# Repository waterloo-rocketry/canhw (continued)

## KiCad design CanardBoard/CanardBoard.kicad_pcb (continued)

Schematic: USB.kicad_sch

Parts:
C47: 22uF; C_0805_2012Metric
C48: 0.1uF; C_0402_1005Metric
F7: 1.5A; Fuse_0805_2012Metric
J9: USB_C_Receptacle_USB2.0_16P; USB_C_Receptacle_GCT_USB4105-xx-A_16P_TopMnt_Horizontal
R45, R46: 5.1k; R_0402_1005Metric; LCSC Part # C17630
U7: USBLC6-2SC6; SOT-23-6

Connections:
+5V_USB: C47.1, C48.1, F7.1, U7.5 (VBUS); also elsewhere on the board
/Processor/USB_D+: U7.4 (I/O2); also elsewhere on the board
/Processor/USB_D-: U7.6 (I/O1); also elsewhere on the board
GND: C47.2, C48.2, J9.A1 (GND), J9.A12 (GND), J9.B1 (GND), J9.B12 (GND), J9.S1 (SHIELD), R45.2, R46.2, U7.2 (GND); also elsewhere on the board
unnamed: F7.2, J9.A4 (VBUS), J9.A9 (VBUS), J9.B4 (VBUS), J9.B9 (VBUS)
unnamed: J9.A5 (CC1), R46.1
unnamed: J9.B5 (CC2), R45.1
unnamed: J9.A6 (D+), J9.B6 (D+), U7.3 (I/O2)
unnamed: J9.A7 (D-), J9.B7 (D-), U7.1 (I/O1)

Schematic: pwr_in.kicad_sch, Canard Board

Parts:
C19, C20, C25, C26: 0.1uF; C_0603_1608Metric; LCSC Part # C49678
C21, C22, C23, C24, C33, C34: 0.1uF; C_0402_1005Metric; LCSC Part # C49678
C27, C28, C29, C30: 10nF; C_0402_1005Metric; LCSC Part # C49678
C31, C32: 0.1uF; C_0805_2012Metric; LCSC Part # C49678
C35, C36: 10uF; C_1210_3225Metric; LCSC Part # C49678
D2, D3: SMAJ28CA; D_SMA
D4, D5, D6, D7: RB520S30T1G; D_SOD-523
F1, F2: 20A; Fuse_1206_3216Metric
J3, J4: XT30PW-M; AMASS_XT30PW-M
Q1, Q2, Q3, Q4: SIR626DP-T1-RE3; PowerPAK_SO-8_Single
Q5, Q6: 2N7002W; Manufacturer_Part_Number 2N7002W
R13, R15, R17, R19, R21, R23, R35, R36, R39, R40: 100k; R_0402_1005Metric; LCSC Part # C17630
R14, R16, R33, R34, R41, R42: 10k; R_0402_1005Metric; LCSC Part # C17630
R18, R20: 3.16k; R_0402_1005Metric; LCSC Part # C17630
R22, R24: 2.2k; R_0402_1005Metric; LCSC Part # C17630
R25, R26: 0R; R_0402_1005Metric; LCSC Part # C17630
R27, R28: 100R; R_0402_1005Metric; LCSC Part # C17630
R29, R30: 1mR; R_Shunt_Vishay_WSKW0612; MPN WSKW06121L000FEA
R31, R32: 10R; R_0402_1005Metric; LCSC Part # C17630
R37, R38: 33k; R_0402_1005Metric; LCSC Part # C17630
TP11: VBAT; TestPoint_Pad_D1.0mm
U4, U5: LM749x0; Manufacturer_Part_Number LM74910QRGERQ1

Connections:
+3V3: D4.1 (K), D6.1 (K), R33.2, R34.2; also elsewhere on the board
+VBAT: C35.1, C36.1, Q3.S, Q4.S, TP11.1, U4.15 (OUT), U5.15 (OUT); also elsewhere on the board
/Power Input/BAT1_IN: C19.1, D2.2 (A2), F1.1, Q1.S, R13.1, R39.1, U4.2 (A)
/Power Input/BAT2_IN: C20.1, D3.2 (A2), F2.1, Q2.S, R15.1, R40.1, U5.2 (A)
/Power Input/BAT_FLT1: R33.1, U4.12 (~FLT); also elsewhere on the board
/Power Input/BAT_FLT2: R34.1, U5.12 (~FLT); also elsewhere on the board
/Power Input/ISENS_BAT1: R37.1, U4.10 (IMON); also elsewhere on the board
/Power Input/ISENS_BAT2: R38.1, U5.10 (IMON); also elsewhere on the board
/Power Input/PWR_EN: Q5.1 (G), Q6.1 (G), R41.2, R42.2; also elsewhere on the board
/Power Input/VSENS_BAT1: D4.2 (A), D5.1 (K), R13.2, R14.1; also elsewhere on the board
/Power Input/VSENS_BAT2: D6.2 (A), D7.1 (K), R15.2, R16.1; also elsewhere on the board
GND: C19.2, C20.2, C21.2, C22.2, C25.2, C26.2, C31.2, C32.2, C33.2, C34.2, C35.2, C36.2, D2.1 (A1), D3.1 (A1), D5.2 (A), D7.2 (A), J3.N, J4.N, Q5.2 (S), Q6.2 (S), R14.2, R16.2, R18.2, R20.2, R22.2, R24.2, R35.2, R36.2, R37.2, R38.2, R41.1, R42.1, U4.13 (GND), U5.13 (GND); also elsewhere on the board
unnamed: C31.1, R31.2
unnamed: C32.1, R32.2
unnamed: F1.2, J3.P
unnamed: F2.2, J4.P
unnamed: Q3.D, R29.1
unnamed: Q4.D, R30.1
unnamed: Q5.3 (D), R39.2, U4.6 (EN), U4.7 (~SLEEP)
unnamed: Q6.3 (D), R40.2, U5.6 (EN), U5.7 (~SLEEP)
unnamed: R27.1, R29.3
unnamed: R28.1, R30.3
unnamed: C23.1, C25.1, Q1.D, R25.1, R29.4, U4.16 (SLEEP_OV), U4.22 (VS), U4.24 (C)
unnamed: C23.2, U4.23 (CAP)
unnamed: C27.1, R27.2, U4.20 (CS+)
unnamed: C27.2, C28.2, R29.2, U4.19 (CS-)
unnamed: Q1.G, U4.1 (DGATE)
unnamed: Q3.G, R31.1, U4.14 (HGATE)
unnamed: R35.1, U4.11 (ILIM)
unnamed: C28.1, R25.2, U4.18 (ISCP)
unnamed: R21.2, R22.1, U4.5 (OV)
unnamed: R17.1, R21.1, U4.3 (SW)
unnamed: C33.1, U4.9 (TMR)
unnamed: C21.1, R17.2, R18.1, U4.4 (UVLO)
unnamed: C24.1, C26.1, Q2.D, R26.1, R30.4, U5.16 (SLEEP_OV), U5.22 (VS), U5.24 (C)
unnamed: C24.2, U5.23 (CAP)
unnamed: C29.1, R28.2, U5.20 (CS+)
unnamed: C29.2, C30.2, R30.2, U5.19 (CS-)
unnamed: Q2.G, U5.1 (DGATE)
unnamed: Q4.G, R32.1, U5.14 (HGATE)
unnamed: R36.1, U5.11 (ILIM)
unnamed: C30.1, R26.2, U5.18 (ISCP)
unnamed: R23.2, R24.1, U5.5 (OV)
unnamed: R19.1, R23.1, U5.3 (SW)
unnamed: C34.1, U5.9 (TMR)
unnamed: C22.1, R19.2, R20.1, U5.4 (UVLO)

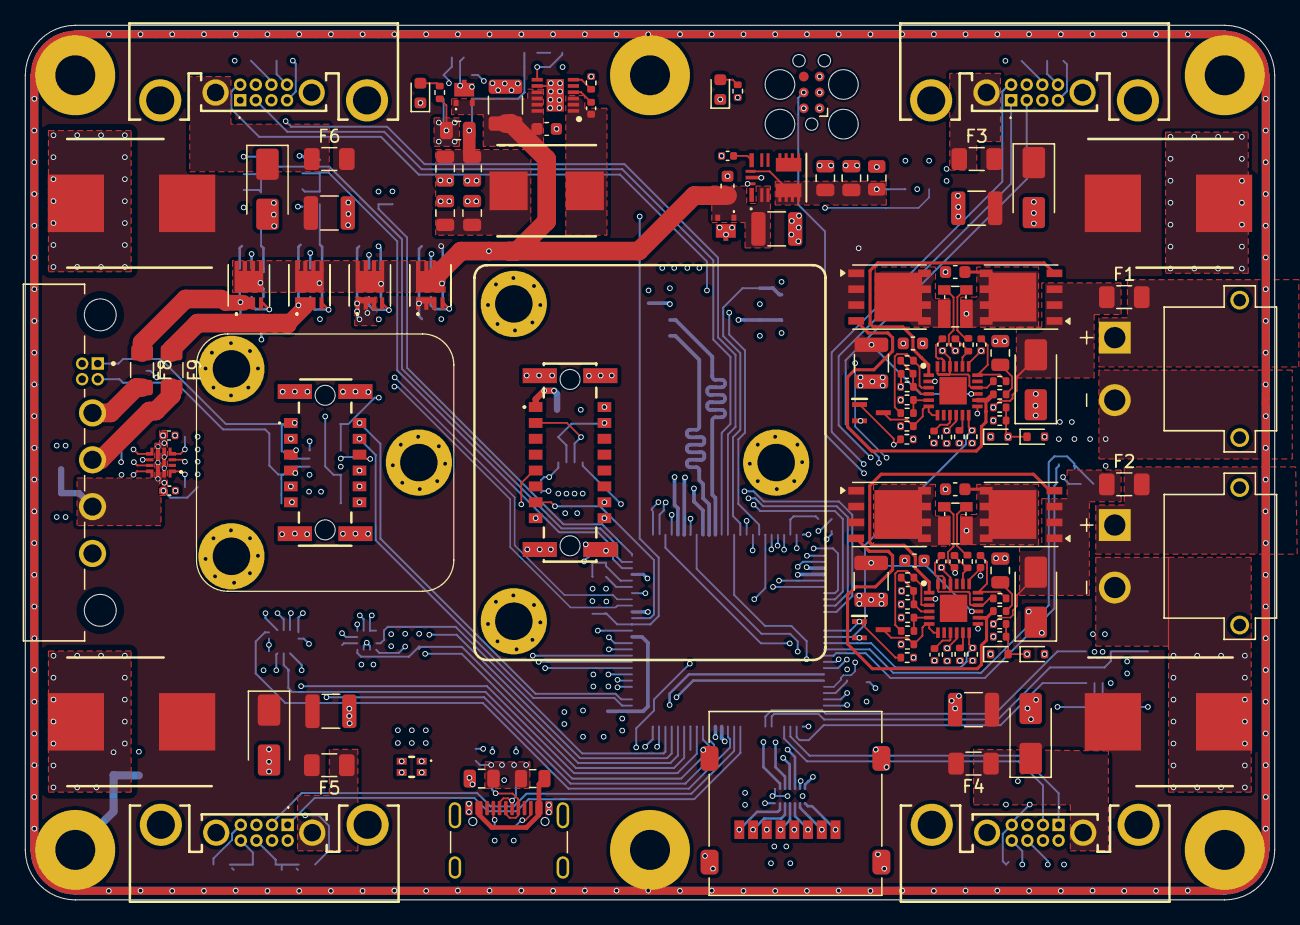
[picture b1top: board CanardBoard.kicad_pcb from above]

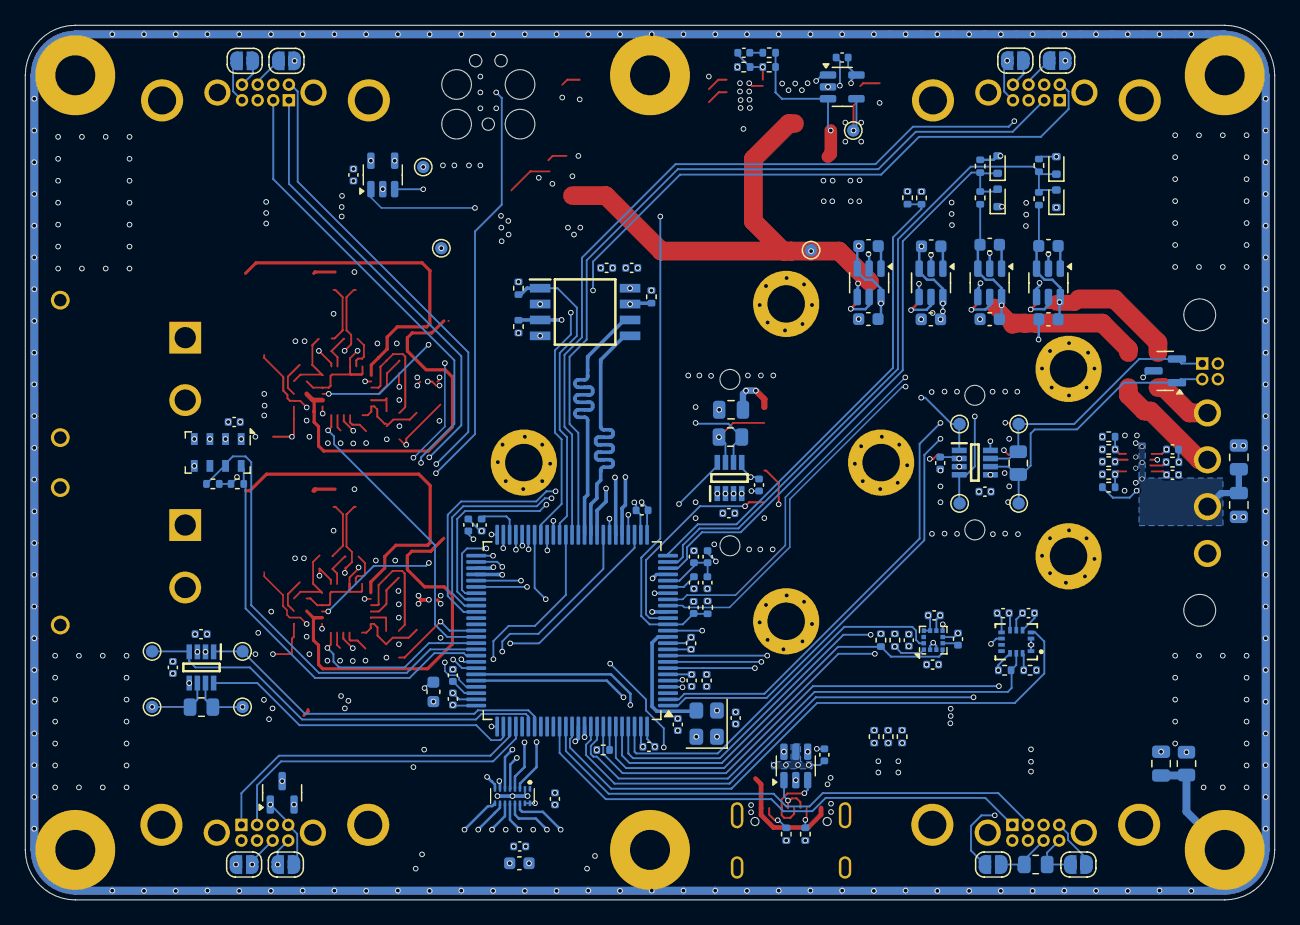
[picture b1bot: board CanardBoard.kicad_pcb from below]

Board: 6 copper layers, 100.0 x 70.0 mm, 266 parts (132 on the bottom side), 184 nets.

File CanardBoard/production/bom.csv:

Designator,Footprint,Quantity,Value,LCSC Part #
"C1, C10, C11, C14, C16, C18, C21, C22, C23, C24, C33, C34, C37, C40, C48, C50, C55, C57, C6, C60, C61, C62, C66, C67, C7, C73, C8, C81, C82, C83, C84, C9, C92, C93",0402,34,0.1uF,C85858
"C12, C17, C47, C56, C63, C65, C74, C76, C89",0805,9,22uF,C86816
"C13, C3, C5, C72, C91",0402,5,1uF,C77007
"C15, C27, C28, C29, C30, C58, C59",0402,7,10nF,C91601
"C19, C20, C25, C26, C51, C52, C53, C54, C70, C71, C85, C86, C87, C88",0603,14,0.1uF,C3011652
"C2, C4, C49",0402,3,2.2uF,C77002
"C31, C32, C90",0805,3,0.1uF,C882587
"C35, C36, C38, C41, C43, C45, C68, C69, C79",1210,9,10uF,C77102
"C39, C42, C44, C46",A786MW227M1HLAV011,4,220uF,A786MW227M1HLAV011
C64,0402,1,220nF,C126524
C75,0402,1,33pF,C126506
"C77, C78",1210,2,47uF,C77101
D1,EAST1616RGBB2,1,LED_RGBA,C6606484
"D10, D17",SOT-23,2,ESDCAN01-2BLY,C1976606
"D11, D12, D8, D9",D_SMA,4,SMAJ28A,C148227
"D13, D14, D15, D16, D4, D5, D6, D7",D_SOD-523,8,RB520S30T1G,C154821
"D18, D19",D_SMF,2,SMF15CA,C1851361
"D2, D3",D_SMA,2,SMAJ28CA,C148228
"D20, D21, D22",0603,3,RED,C2986060
"F1, F2",1206,2,20A,C2838910
"F3, F4, F5, F6",1206,4,10A,C41367232
"F7, F8",1206,2,1.5A,C883133
F9,1206,1,5A,C41367229
FB1,0402,1,BLM15AG121SN1D,C85812
J10,connector_Harwin_G125-MH104M4-04AD000P,1,G125-MH104M4-04AD000P,
J11,Movella-1374028,1,Movella-1374028,
J12,1374027,1,1374027,
J2,microSD_HC_Molex_47219-2001,1,Micro_SD_Card,C164170
"J3, J4",AMASS_XT30PW-M,2,XT30PW-M,
J5,G125MH10805M41AD1ADP,1,Motor 2,
J6,G125MH10805M41AD1ADP,1,Motor 1,
J7,G125MH10805M41AD1ADP,1,Motor 4,
J8,G125MH10805M41AD1ADP,1,Motor 3,
J9,USB_C_Receptacle_GCT_USB4105-xx-A_16P_TopMnt_Horizontal,1,USB_C_Receptacle_USB2.0_16P,C165948
L1,SRP7050WA,1,4.7uH,C19947706
"Q1, Q2, Q3, Q4",PowerPAK_SO-8_Single,4,SIR626DP-T1-RE3,
"Q10, Q7, Q8, Q9",Infineon-PG-TSDSON-8,4,20N06D,C7543835
"Q5, Q6",2N7002W,2,2N7002W,C232391
"R1, R14, R16, R2, R33, R34, R37, R38, R41, R42, R47, R48, R49, R8",0402,14,10k,C144807
"R13, R15, R17, R19, R21, R23, R35, R36, R39, R40, R50, R52, R54, R55, R56, R59, R61, R67",0402,18,100k,C144809
"R18, R20",0402,2,3.16k,C227034
"R22, R24, R6, R7",0402,4,2.2k,C144773
"R25, R26",0402,2,0R,C226739
"R27, R28, R4, R5",0402,4,100R,C144808
"R29, R30",R_Shunt_Vishay_WSKW0612,2,1mR,C1517439
"R3, R72, R73",0402,3,330R,C226996
"R31, R32",0402,2,10R,C144805
"R43, R44, R65",0805,3,120R,C727984
"R45, R46",0402,2,5.1k,C144745
"R51, R53, R68",0402,3,19.1k,C226835
R57,0402,1,34k,C227006
R58,0402,1,681R,C416567
R60,0805,1,120R,
R62,0402,1,43.2k,C278596
"R63, R64, R69, R74, R75",0402,5,1k,C144789
R66,0402,1,0R,
"R70, R71",0805,2,5m,C728267
R76,0805,1,1M,C228604
R9,1206,1,5.1k,
U1,LQFP-100_14x14mm_P0.5mm,1,STM32H733VGTx,
"U10, U11, U12, U9",SOT-23-6,4,LM74700,
"U13, U16, U6",TCAN3413DDFR,3,TCAN3413DDFR,
U14,TPS25947xx,1,TPS259472,C3662789
U15,LGA-12_2x2mm_P0.5mm,1,LSM303AGR,
U17,LMR51460,1,LMR51460,C41802645
U18,TPSM33606S3QRDNRQ1,1,TPSM33610S3QRDNRQ1,
"U19, U20",SOT-23-5,2,INA180A3,C122882
U2,LGA-8_3x5mm_P1.25mm,1,MS5611-01BA,
U21,LSM6DSV32XTR,1,LSM6DSV32XTR,
U22,EMIF06MSD02N16,1,EMIF06-MSD02N16,C5267594
"U23, U3",WSON-6-1EP_2x2mm_P0.65mm_EP1x1.6mm,2,TVS3300DRV,C2863624
U24,TPS22975DSGR,1,TPS22975DSGR,
"U4, U5",LM749x0,2,LM749x0,
U7,SOT-23-6,1,USBLC6-2SC6,C7519
U8,MX25L25645GM2I-08G,1,MX25L25645GM2I-08G,
X1,Oscillator_SMD_Abracon_ASE-4Pin_3.2x2.5mm,1,ASE-4.000MHZ-L-C-T,C437121

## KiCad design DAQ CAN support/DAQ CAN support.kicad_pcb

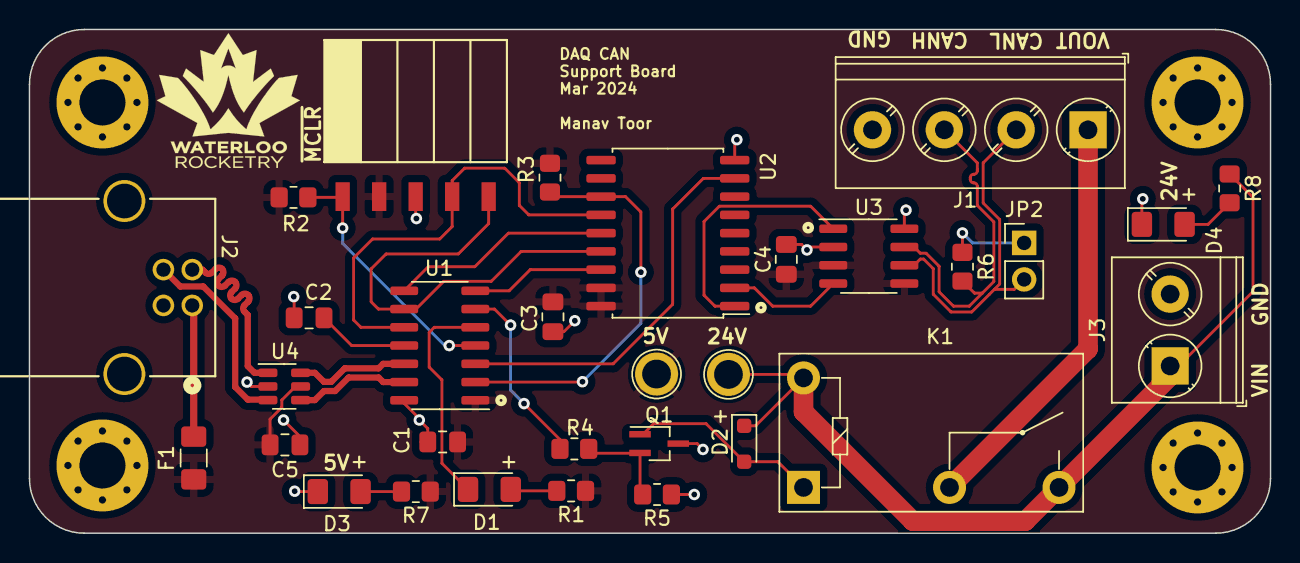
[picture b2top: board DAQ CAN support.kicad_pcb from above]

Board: 2 copper layers, 86.4 x 35.1 mm, 35 parts (0 on the bottom side), 27 nets.

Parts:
5V, 24V: TestPoint; TestPoint_Plated_Hole_D2.0mm
C1, C2, C3, C5: 0.1u; C_0805_2012Metric_Pad1.18x1.45mm_HandSolder
C4: 10u; C_0805_2012Metric_Pad1.18x1.45mm_HandSolder
D1, D3, D4: Red; LED_1206_3216Metric_Pad1.42x1.75mm_HandSolder
D2: 1N4148WX-TP; D_SOD-323_HandSoldering
F1: 350 mA PTC; Fuse_1206_3216Metric_Pad1.42x1.75mm_HandSolder
H1, H2, H3, H4: MountingHole_Pad; MountingHole_3.2mm_M3_Pad_Via
J1: Screw_Terminal_01x04; TerminalBlock_Phoenix_PT-1,5-4-5.0-H_1x04_P5.00mm_Horizontal
J2: USB_B; CONN_USB-B1HSW6_OST
J3: Screw_Terminal_01x02; TerminalBlock_Phoenix_PT-1,5-2-5.0-H_1x02_P5.00mm_Horizontal
J4: Programming Header; PinHeader_5x2.54_SMD_90deg_952-3198-1-ND
JP2: Jumper_2_Open; PinHeader_1x02_P2.54mm_Vertical
K1: G5Q-1A; Relay_SPST_Omron-G5Q-1A
Q1: DMN63D8LW-13; SOT-323_SC-70_Handsoldering
R1: 330R; R_0805_2012Metric_Pad1.20x1.40mm_HandSolder
R2, R3, R5: 10k; R_0805_2012Metric_Pad1.20x1.40mm_HandSolder
R4: 250R; R_0805_2012Metric_Pad1.20x1.40mm_HandSolder
R6: 120R; R_0805_2012Metric_Pad1.20x1.40mm_HandSolder
R7: 150R; R_0805_2012Metric_Pad1.20x1.40mm_HandSolder
R8: 1.1k; R_0805_2012Metric_Pad1.20x1.40mm_HandSolder
U1: PIC16F1455; SOIC-14_3.9x8.7mm_P1.27mm
U2: MCP2515; SOIC-18W_7.5x11.6mm_P1.27mm
U3: MCP2562; SOIC-8_3.9x4.9mm_P1.27mm
U4: USBLC6-2SC6; SOT-23-6

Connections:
+5V: 5V.1, C1.1, C3.1, C4.1, C5.1, F1.2, J4.2 (Pin_4), R1.1, R2.1, R3.2, R7.1, U1.1 (VDD), U2.17 (~RESET), U2.18 (VDD), U3.3 (VDD), U3.5 (VIO), U4.5 (VBUS)
+24V: 24V.1, D2.1 (K), J3.1, K1.3, K1.5, R8.1
/CAN+: J1.3, R6.2, U3.7 (CANH)
/CAN-: J1.2, JP2.2 (B), U3.6 (CANL)
/CAN_INT: R3.1, U1.2 (RA5), U2.12 (~INT)
/CLKOUT: U1.3 (RA4), U2.8 (OSC1)
/CS: U1.7 (RC3), U2.16 (~CS)
/MISO: J4.5 (Pin_1), U1.9 (RC1/ICSPCLK), U2.15 (SO)
/MOSI: U1.8 (RC2), U2.14 (SI)
/RELAY_CONTROL: R4.1, U1.6 (RC4)
/SCK: J4.4 (Pin_2), U1.10 (RC0/ICSPDAT), U2.13 (SCK)
/USB_D+: J2.3 (D+), U1.13 (RA0/D+), U4.3 (I/O1), U4.4 (I/O2)
/USB_D-: J2.2 (D-), U1.12 (RA1/D-), U4.1 (I/O1), U4.6 (I/O2)
/VOUT: J1.1, K1.2
GND: C1.2, C2.2, C3.2, C4.2, C5.2, D3.1 (K), D4.1 (K), H1.1, H2.1, H3.1, H4.1, J1.4, J2.4 (GND), J2.5 (Shield), J3.2, J4.3, Q1.3 (S), R5.1, U1.14 (VSS), U2.9 (VSS), U3.2 (VSS), U3.8 (STBY), U4.2 (GND)
unnamed: D1.2 (A), R1.2
unnamed: D1.1 (K), U1.5 (RC5)
unnamed: D2.2 (A), K1.1, Q1.1 (D)
unnamed: D3.2 (A), R7.2
unnamed: D4.2 (A), R8.2
unnamed: F1.1, J2.1 (VBUS)
unnamed: J4.1 (Pin_5), R2.2, U1.4 (RA3/~MCLR)
unnamed: JP2.1 (A), R6.1
unnamed: Q1.2 (G), R4.2, R5.2
unnamed: C2.1, U1.11 (VUSB3V3)
unnamed: U2.2 (RXCAN), U3.4 (RXD)
unnamed: U2.1 (TXCAN), U3.1 (TXD)

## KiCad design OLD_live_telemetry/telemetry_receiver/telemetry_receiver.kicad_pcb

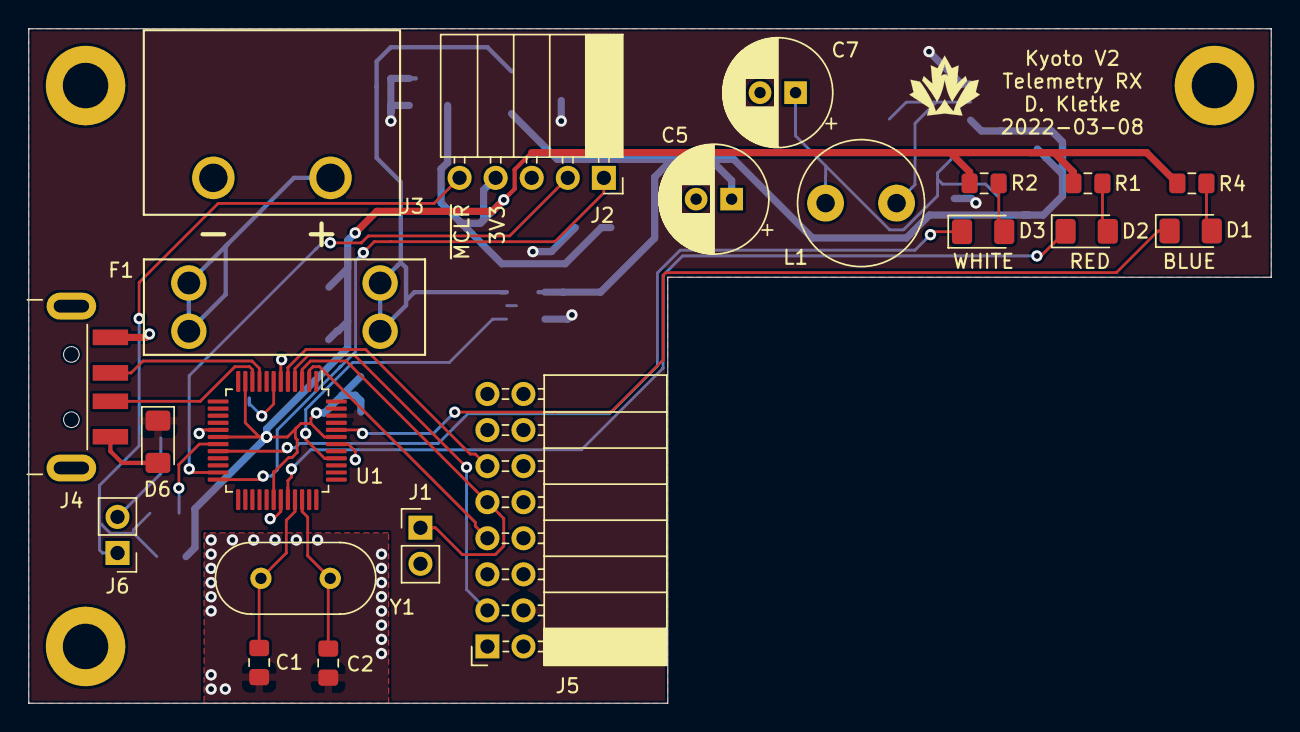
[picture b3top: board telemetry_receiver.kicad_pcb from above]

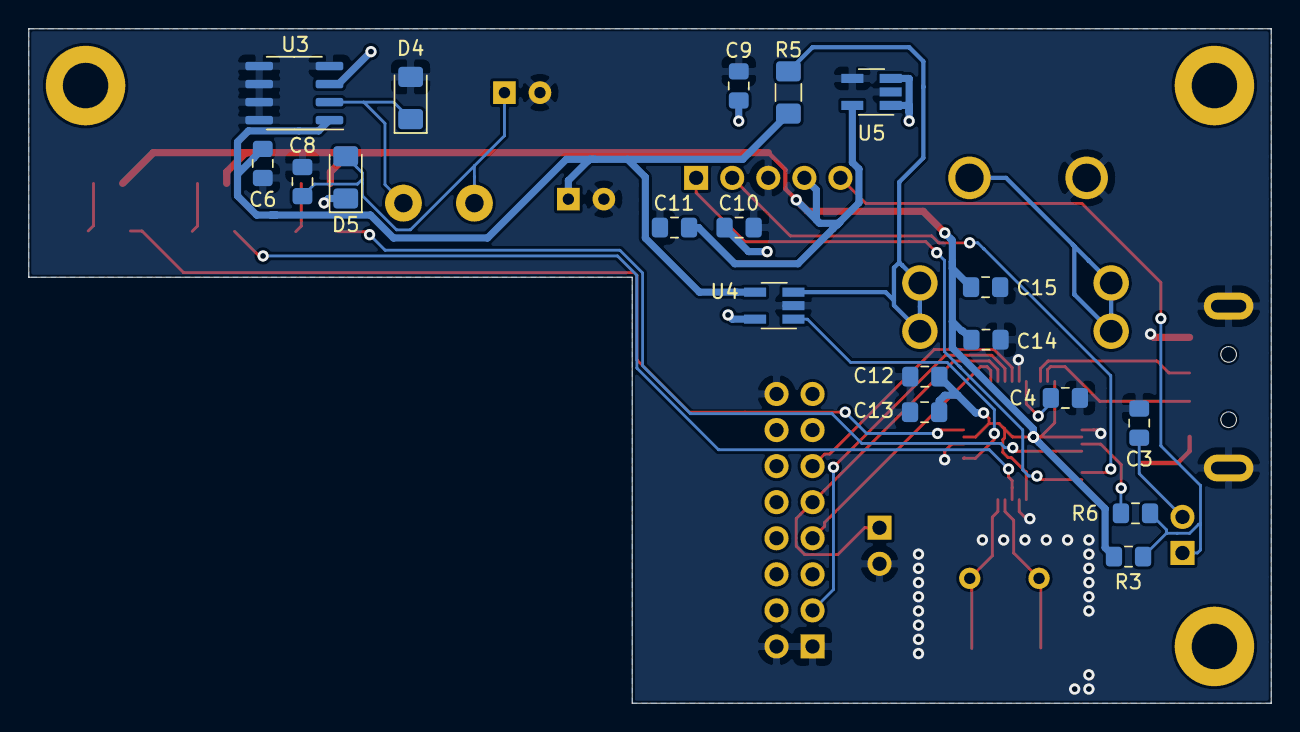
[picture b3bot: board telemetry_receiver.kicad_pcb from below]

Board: 2 copper layers, 87.5 x 47.5 mm, 40 parts (19 on the bottom side), 30 nets.

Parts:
C1, C2: 27pF; C_0805_2012Metric_Pad1.15x1.40mm_HandSolder
C3, C6, C8, C9, C12, C13, C14, C15: 0.1uF; C_0805_2012Metric_Pad1.15x1.40mm_HandSolder
C4: 10uF; C_0805_2012Metric_Pad1.15x1.40mm_HandSolder
C5, C7: 100uF; CP_Radial_D7.5mm_P2.50mm
C10, C11: 1uF; C_0805_2012Metric_Pad1.15x1.40mm_HandSolder
D1, D2, D3: LED; LED_1206_3216Metric_Pad1.42x1.75mm_HandSolder
D4, D5, D6: SD1206S040S2R0; D_1206_3216Metric_Pad1.42x1.75mm_HandSolder
F1: F4989-ND, 36-3557-2-ND; Fuseholder_36-3557-15-ND
J1: Bootload Short; PinHeader_1x02_P2.54mm_Vertical
J2: Programming Header; PinSocket_1x05_P2.54mm_Horizontal
J3: Battery In; BarrierBlock_ED2945-ND
J4: USB_A; USB_A_CNCTech_1001-011-01101_Horizontal
J5: RFD900x RADIO MODEM CONN; PinSocket_2x08_P2.54mm_Horizontal
J6: ~MCLR~ Cap Jumper; PinHeader_1x02_P2.54mm_Vertical
L1: 47uH; L_Radial_D8.7mm_P5.00mm_Fastron_07HCP
R1, R2, R4: 130; R_0805_2012Metric_Pad1.15x1.40mm_HandSolder
R3: 10k; R_0805_2012Metric_Pad1.15x1.40mm_HandSolder
R5: R_sense; R_1206_3216Metric_Pad1.42x1.75mm_HandSolder
R6: 100R; R_0805_2012Metric_Pad1.15x1.40mm_HandSolder
U1: PIC24FJ64GU205; TQFP-48_7x7mm_P0.5mm
U3: AP1509; SOIC-8_3.9x4.9mm_P1.27mm
U4: INA180; SOT-23-5_HandSoldering
U5: 497-18013-1-ND; SOT-23-5_HandSoldering
Y1: Crystal; Crystal_HC49-U_Vertical

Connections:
+3V3: C11.1, C12.1, C13.1, C14.1, C15.1, J2.4, R1.1, R2.1, R3.1, R4.1, U1.11, U1.18, U1.30, U1.43, U5.5
+5V: C9.2, C10.1, D5.1, D6.1, J5.4, U1.46, U3.3, U4.5, U5.1, U5.3
+12V: C5.1, C6.1, R5.1, U3.1, U4.4
/ICSPCLK: J2.1, U1.24
/ICSPDAT: J2.2, U1.23
/OSC1: C1.1, U1.33, Y1.1
/OSC2: C2.2, U1.34, Y1.2
/USB_D+: J4.3, U1.9
/USB_D-: J4.2, U1.10
/power/CURR_BATT: U1.40, U4.1
/radio.sch/RX: J5.7, U1.2
/radio.sch/TX: J1.1, J5.9, U1.3
/radio.sch/~CTS: J5.3, U1.4
/radio.sch/~RTS: J5.11, U1.5
/~MCLR: J2.5, J6.1, R3.2, R6.1
GND: C1.2, C2.1, C3.2, C4.2, C5.2, C6.2, C7.2, C8.2, C9.1, C10.2, C11.2, C12.2, C13.2, C14.2, C15.2, D4.2, J1.2, J2.3, J3.1, J4.4, J4.5, J5.1, J5.2, J5.16, U1.6, U1.17, U1.31, U1.42, U3.4, U3.5, U3.6, U3.7, U3.8, U4.2, U5.2, U5.4
unnamed: C3.1, J6.2
unnamed: C4.1, U1.7
unnamed: C7.1, C8.1, D5.2, L1.2
unnamed: D1.1, U1.44
unnamed: D1.2, R4.2
unnamed: D2.1, U1.32
unnamed: D2.2, R1.2
unnamed: D3.1, U1.20
unnamed: D3.2, R2.2
unnamed: D4.1, L1.1, U3.2
unnamed: D6.2, J4.1
unnamed: F1.1, R5.2, U4.3
unnamed: F1.2, J3.2
unnamed: R6.2, U1.19

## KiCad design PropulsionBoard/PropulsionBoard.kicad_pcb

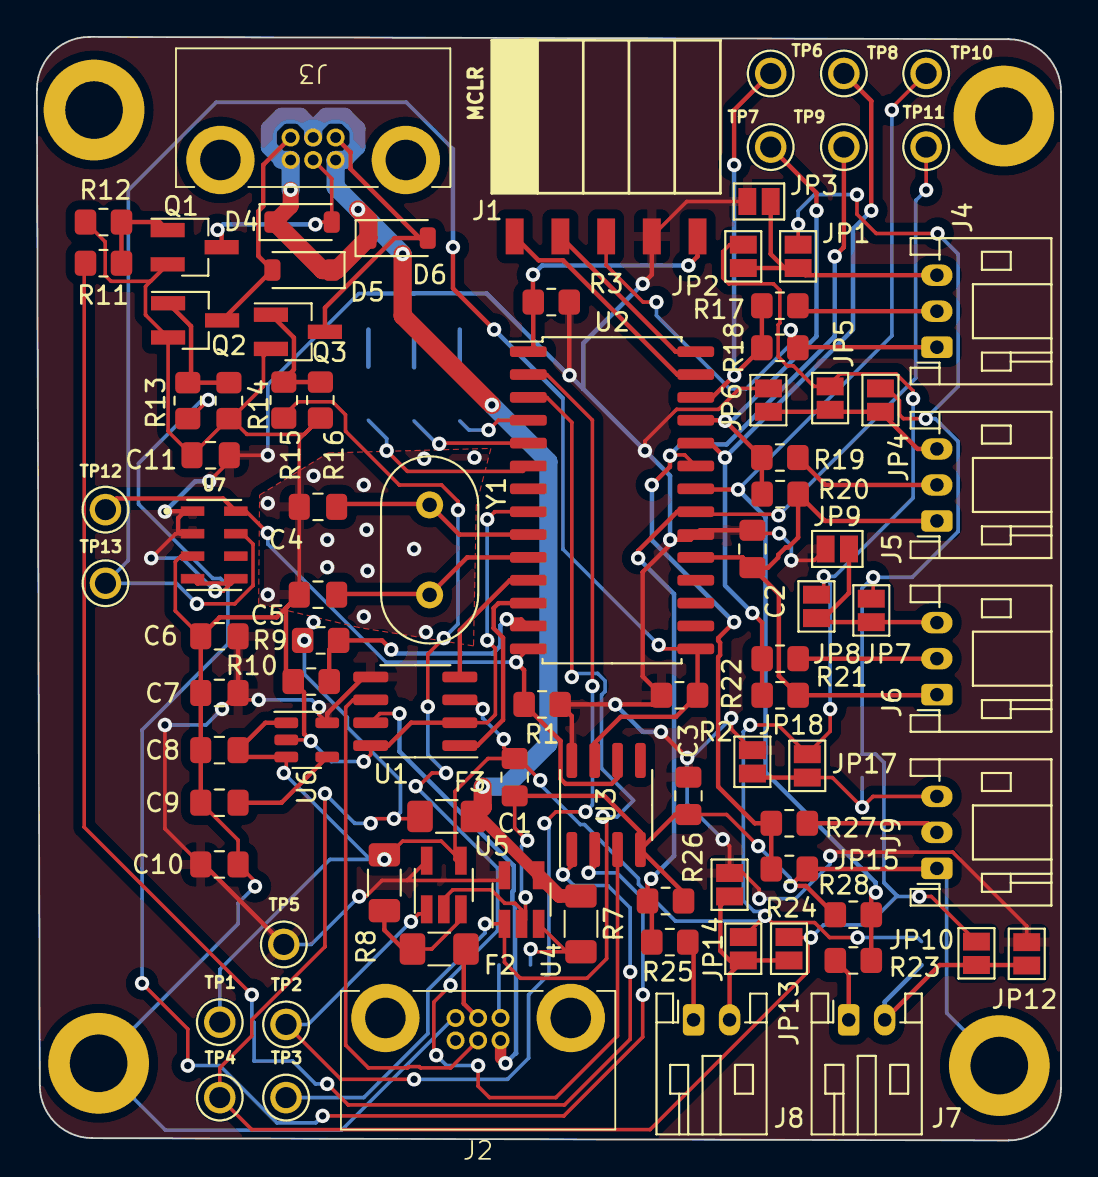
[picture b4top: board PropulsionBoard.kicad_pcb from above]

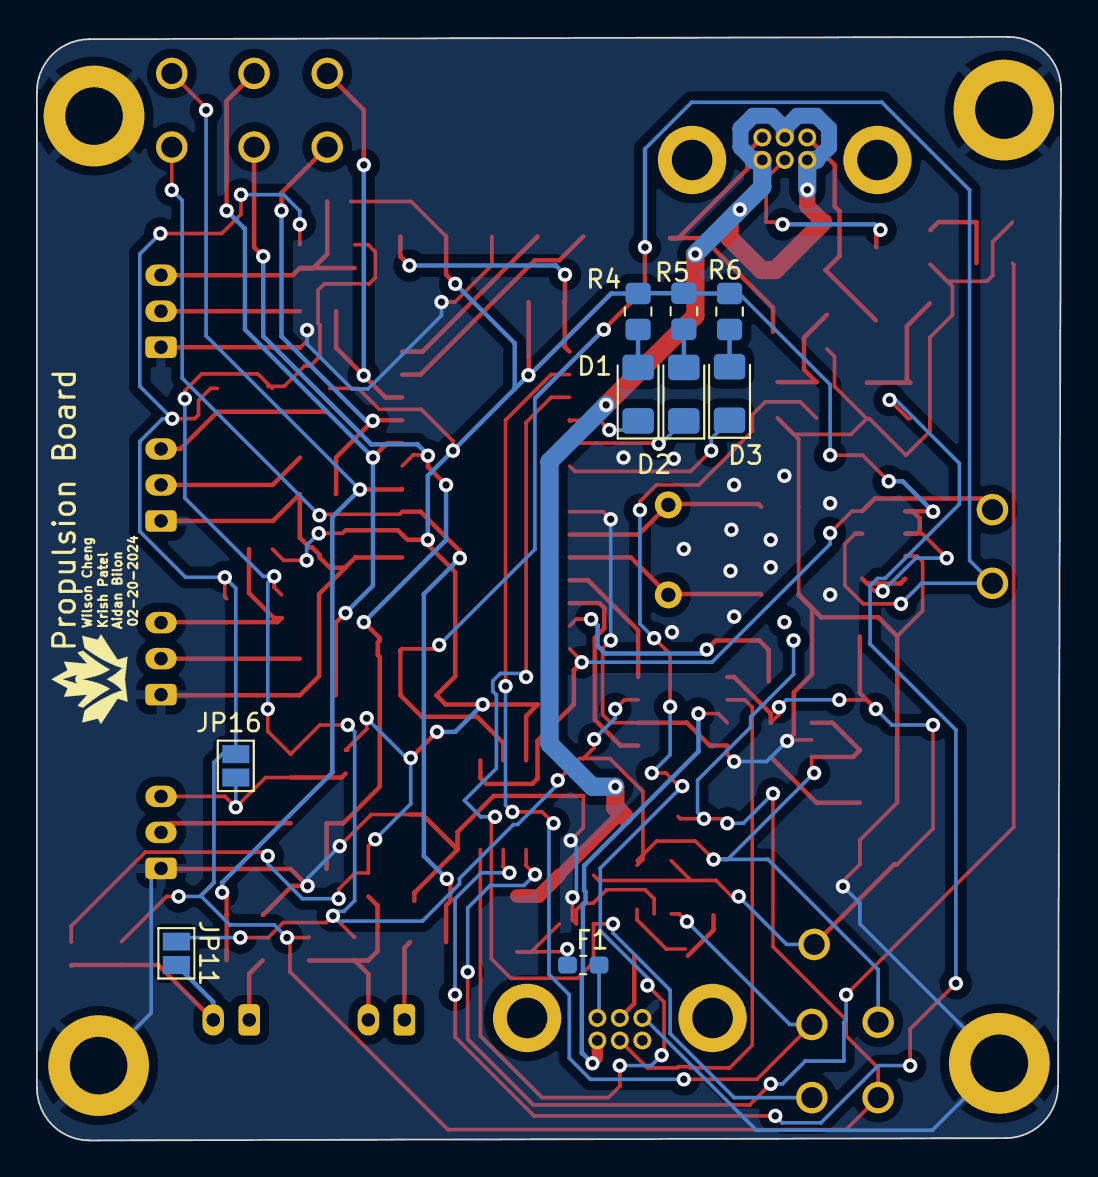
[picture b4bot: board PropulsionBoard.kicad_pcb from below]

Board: 2 copper layers, 56.9 x 61.3 mm, 99 parts (9 on the bottom side), 57 nets.

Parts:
C1: 10 uF; C_0805_2012Metric_Pad1.18x1.45mm_HandSolder
C2, C3, C6, C7, C11: 0.1 uF; C_0805_2012Metric_Pad1.18x1.45mm_HandSolder
C4, C5: 27 pF; C_0805_2012Metric_Pad1.18x1.45mm_HandSolder
C8: 1 uF; C_0805_2012Metric_Pad1.18x1.45mm_HandSolder
C9: 10 nF; C_0805_2012Metric_Pad1.18x1.45mm_HandSolder
C10: 2.2 uF; C_0805_2012Metric_Pad1.18x1.45mm_HandSolder
D1: LED_GREEN; LED_1206_3216Metric_Pad1.42x1.75mm_HandSolder
D2: LED_BLUE; LED_1206_3216Metric_Pad1.42x1.75mm_HandSolder
D3: LED_RED; LED_1206_3216Metric_Pad1.42x1.75mm_HandSolder
D4, D5, D6: BAS16GWJ; D_SOD-123
F1: Fuse 0603 ERB-RE2R00V; Fuse_0603_1608Metric_Pad1.05x0.95mm_HandSolder
F2, F3: Polyfuse 350 mA; Fuse_1206_3216Metric_Pad1.42x1.75mm_HandSolder
J1: Programming Header; PinHeader_5x2.54_SMD_90deg_952-3198-1-ND
J2: CAN_Connector; connector_Harwin_G125–MG10605M4P
J3: Valve Connection; connector_Harwin_G125–MG10605M4P
J4, J5, J6, J9: Conn_01x03_Female; JST_PH_S3B-PH-K_1x03_P2.00mm_Horizontal
J7, J8: Conn_01x02_Female-Connector; JST_PH_S2B-PH-K_1x02_P2.00mm_Horizontal
JP1, JP4, JP7, JP10, JP13, JP16: +12V; SolderJumper-2_P1.3mm_Open_Pad1.0x1.5mm
JP2, JP5, JP8, JP11, JP14, JP17: +5V; SolderJumper-2_P1.3mm_Open_Pad1.0x1.5mm
JP3, JP6, JP9, JP12, JP15, JP18: +3.3V; SolderJumper-2_P1.3mm_Open_Pad1.0x1.5mm
Q1, Q2, Q3: SI3420A-TP; SOT-23_Handsoldering
R1, R2, R3, R10, R12, R14, R16: 10K; R_0805_2012Metric_Pad1.20x1.40mm_HandSolder
R4, R5, R6: 100R; R_0805_2012Metric_Pad1.20x1.40mm_HandSolder
R7: 15 mR; R_1206_3216Metric_Pad1.30x1.75mm_HandSolder
R8: 62 mR; R_1206_3216Metric_Pad1.30x1.75mm_HandSolder
R9: 30K; R_0805_2012Metric_Pad1.20x1.40mm_HandSolder
R11, R13, R15: 270R; R_0805_2012Metric_Pad1.20x1.40mm_HandSolder
R17, R19, R21, R23, R24, R25, R26, R27: TBD; R_0805_2012Metric_Pad1.20x1.40mm_HandSolder
R18, R20, R22, R28: 90mR; R_0805_2012Metric_Pad1.20x1.40mm_HandSolder
TP1: TP_5V; KEYSTONE_5000
TP2: CURRAMP5V; KEYSTONE_5000
TP3: CURRAMP12V; KEYSTONE_5000
TP4: TP_12V; KEYSTONE_5000
TP5: TP_3.3V; KEYSTONE_5000
TP6: TP_S1A-OUT; KEYSTONE_5000
TP7: TP_S2A-OUT; KEYSTONE_5000
TP8: TP_S3A-OUT; KEYSTONE_5000
TP9: TP_S4A-OUT; KEYSTONE_5000
TP10: TP_S5-OUT; KEYSTONE_5000
TP11: TP_S6-OUT; KEYSTONE_5000
TP12: TP_SCL; KEYSTONE_5000
TP13: TP_SDA; KEYSTONE_5000
U1: MC2562; SOIC-8_3.9x4.9mm_P1.27mm
U2: PIC18F26K83; SOIC-28W_7.5x17.9mm_P1.27mm
U3: PCA9536DR; SOIC-8_3.9x4.9mm_P1.27mm
U4, U5: INA180; SOT-23-5_HandSoldering
U6: SPX3819M5-L-3-3; SOT-23-5
U7: MS5607-02BA03; SON125P300X500X100-8N
Y1: Crystal; Resonator-2Pin_W10.0mm_H5.0mm

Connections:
+3V3: C2.2, C3.1, C6.2, C7.2, C10.1, C11.2, J1.4, JP3.1 (A), JP6.1 (A), JP9.1 (A), JP12.1 (A), JP15.1 (A), JP18.1 (A), R1.1, R2.1, R3.1, R4.2, R5.2, R6.2, TP5.1, U1.5 (VIO), U2.20 (VDD), U3.8 (VCC), U4.5 (VS), U5.5 (VS), U6.5 (OUT), U7.1 (VDD), U7.2 (PS), U7.4 (CSB), U7.5 (CSB)
+5V: C1.1, C8.1, JP2.1 (A), JP5.1 (A), JP8.1 (A), JP11.1 (A), JP14.1 (A), JP17.1 (A), R8.1, TP1.1, U1.3 (VDD), U5.4 (IN-), U6.1 (IN), U6.3 (EN)
+12V: F3.1, JP1.1 (A), JP4.1 (A), JP7.1 (A), JP10.1 (A), JP13.1 (A), JP16.1 (A), R9.1, TP4.1
/Analog Sensor/SENSOR1: R17.2, R18.1, TP6.1, U2.26 (RB5)
/Analog Sensor/SENSOR2: R19.2, R20.1, TP7.1, U2.25 (RB4)
/Analog Sensor/SENSOR3: R21.2, R22.1, TP8.1, U2.24 (RB3)
/Analog Sensor/SENSOR4: R27.2, R28.1, TP9.1, U2.23 (RB2)
/Analog Sensor/SENSOR5: R23.2, R24.1, TP10.1, U2.22 (RB1)
/Analog Sensor/SENSOR6: R25.2, R26.1, TP11.1, U2.21 (RB0)
/Digital Sensor Suite/SCL: R1.2, TP12.1, U2.14 (RC3), U3.6 (SCL), U7.8 (SCLK)
/Digital Sensor Suite/SDA: R2.2, TP13.1, U2.15 (RC4), U3.7 (SDA), U7.7 (SDA)
/MCU/CAN_RX: U1.4 (RXD), U2.11 (RC0)
/MCU/CAN_TX: U1.1 (TXD), U2.12 (RC1)
/MCU/CURR_INPUT_5V: TP2.1, U2.2 (RA0), U5.1 (VO)
/MCU/CURR_INPUT_12V: TP3.1, U2.3 (RA1), U4.1 (VO)
/MCU/ICSPCLK: J1.1, U2.27 (RB6/ICSPCLK)
/MCU/ICSPDAT: J1.2, U2.28 (RB7/ICSPDAT)
/MCU/LED_BLUE: D2.1 (K), U2.5 (RA3)
/MCU/LED_GREEN: D1.1 (K), U2.4 (RA2)
/MCU/LED_RED: D3.1 (K), U2.6 (RA4)
/MCU/OSC1: C4.1, U2.9 (RA7/OSC1), Y1.1
/MCU/OSC2: C5.1, U2.10 (RA6/OSC2), Y1.2
/MCU/VALVE_CONTROL_1: R11.2, U3.1 (P0)
/MCU/VALVE_CONTROL_2: R13.2, U3.2 (P1)
/MCU/VALVE_CONTROL_3: R15.2, U3.3 (P2)
/MCU/VBAT: R9.2, R10.1, U2.13 (RC2)
/MCU/~MCLR: J1.5, R3.2, U2.1 (~MCLR)
/Valve Control/RELAY1_-: D4.2 (A), J3.2, Q1.3 (D)
/Valve Control/RELAY2_-: D5.2 (A), J3.4, Q2.3 (D)
/Valve Control/RELAY3_-: D6.2 (A), J3.6, Q3.3 (D)
Actuator_Power: D4.1 (K), D5.1 (K), D6.1 (K), F3.2, J3.1, J3.3, J3.5, R7.1, U4.4 (IN-)
CANH: J2.4, U1.7 (CANH)
CANL: J2.5, U1.6 (CANL)
GND: C1.2, C2.1, C3.2, C4.2, C5.2, C6.1, C7.1, C8.2, C9.2, C10.2, C11.1, J1.3, J2.3, J4.1, J5.1, J6.1, J9.1, Q1.2 (S), Q2.2 (S), Q3.2 (S), R10.2, R12.2, R14.2, R16.2, R18.2, R20.2, R22.2, R24.2, R26.2, R28.2, U1.2 (VSS), U1.8 (STBY), U2.8 (VSS), U2.19 (VSS), U3.4 (GND), U4.2 (GND), U5.2 (GND), U6.2 (GND), U7.3 (GND)
unnamed: D1.2 (A), R4.1
unnamed: D2.2 (A), R5.1
unnamed: D3.2 (A), R6.1
unnamed: F1.2, J2.1
unnamed: F2.2, J2.2
unnamed: J4.2, R17.1
unnamed: J4.3, JP1.2 (B), JP2.2 (B), JP3.2 (B)
unnamed: J5.2, R19.1
unnamed: J5.3, JP4.2 (B), JP5.2 (B), JP6.2 (B)
unnamed: J6.2, R21.1
unnamed: J6.3, JP7.2 (B), JP8.2 (B), JP9.2 (B)
unnamed: J7.1, R23.1
unnamed: J7.2, JP10.2 (B), JP11.2 (B), JP12.2 (B)
unnamed: J8.1, R25.1
unnamed: J8.2, JP13.2 (B), JP14.2 (B), JP15.2 (B)
unnamed: J9.2, R27.1
unnamed: J9.3, JP16.2 (B), JP17.2 (B), JP18.2 (B)
unnamed: Q1.1 (G), R11.1, R12.1
unnamed: Q2.1 (G), R13.1, R14.1
unnamed: Q3.1 (G), R15.1, R16.1
unnamed: F1.1, R7.2, U4.3 (IN+)
unnamed: F2.1, R8.2, U5.3 (IN+)
unnamed: C9.1, U6.4 (BP)

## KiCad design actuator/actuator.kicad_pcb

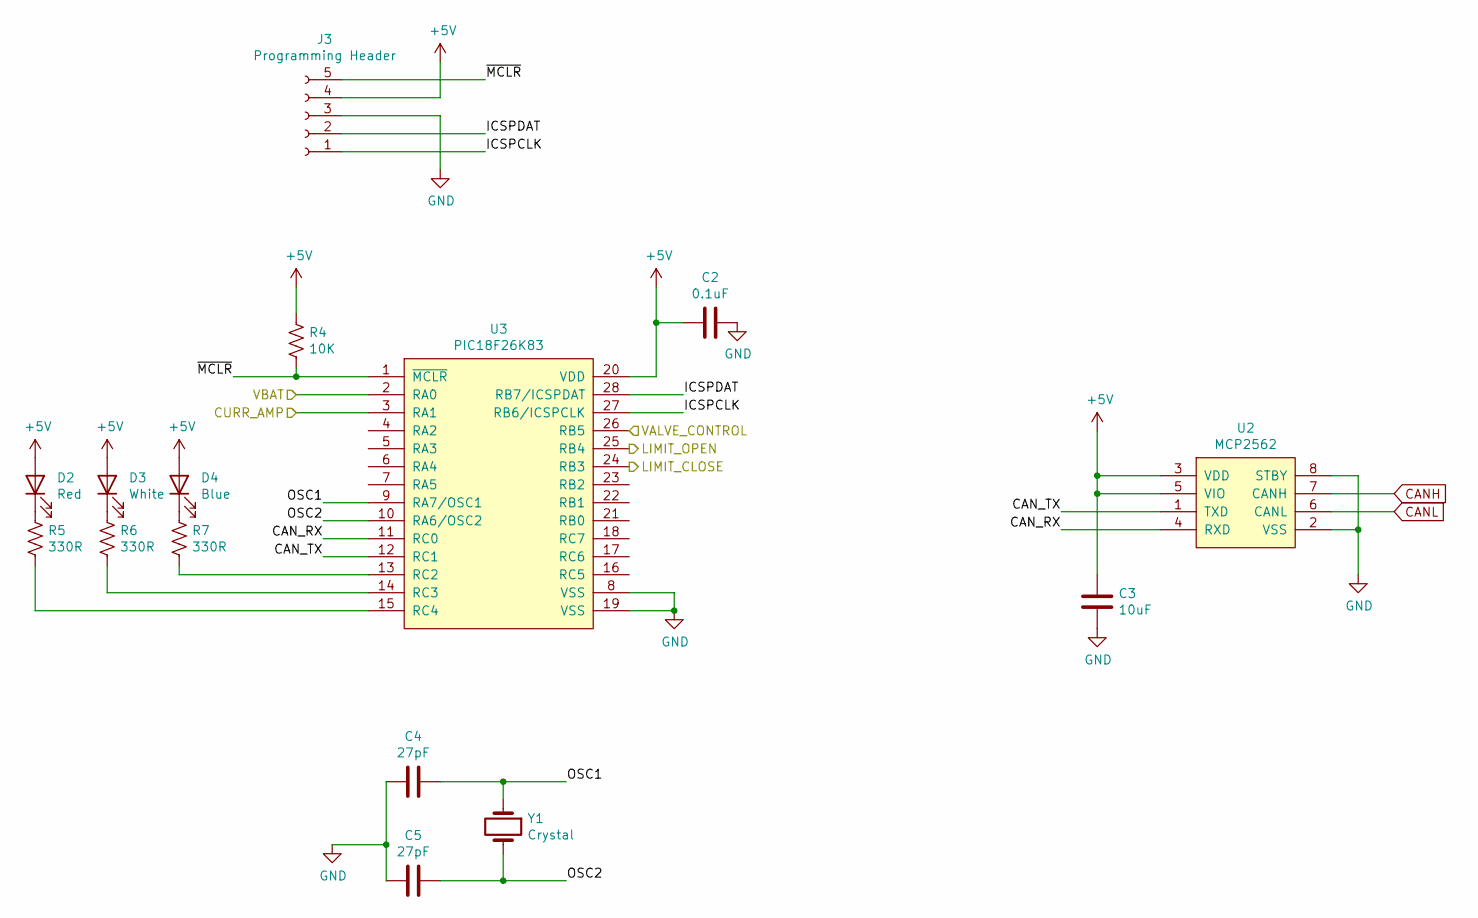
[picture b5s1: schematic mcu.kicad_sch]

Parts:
C2: 0.1uF; C_0805_2012Metric
C3: 10uF; C_0805_2012Metric_Pad1.15x1.40mm_HandSolder
C4, C5: 27pF; C_0805_2012Metric
D2: Red; LED_1206_3216Metric_Pad1.42x1.75mm_HandSolder
D3: White; LED_1206_3216Metric_Pad1.42x1.75mm_HandSolder
D4: Blue; LED_1206_3216Metric_Pad1.42x1.75mm_HandSolder
J3: Programming Header; PinHeader_5x2.54_SMD_90deg_952-3198-1-ND
R4: 10K; R_0805_2012Metric
R5, R6, R7: 330R; R_0805_2012Metric
U2: MCP2562; SOIC-8_3.9x4.9mm_P1.27mm
U3: PIC18F26K83; SOIC-28W_7.5x17.9mm_P1.27mm
Y1: Crystal; Crystal_HC49-4H_Vertical

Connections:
+5V: C2.2, C3.1, D2.2 (A), D3.2 (A), D4.2 (A), J3.4, R4.1, U2.3 (VDD), U2.5 (VIO), U3.20 (VDD); also elsewhere on the board
/MCU/CAN_RX: U2.4 (RXD), U3.11 (RC0)
/MCU/CAN_TX: U2.1 (TXD), U3.12 (RC1)
/MCU/CURR_AMP: U3.3 (RA1); also elsewhere on the board
/MCU/ICSPCLK: J3.1, U3.27 (RB6/ICSPCLK)
/MCU/ICSPDAT: J3.2, U3.28 (RB7/ICSPDAT)
/MCU/LIMIT_CLOSE: U3.24 (RB3); also elsewhere on the board
/MCU/LIMIT_OPEN: U3.25 (RB4); also elsewhere on the board
/MCU/OSC1: C4.1, U3.9 (RA7/OSC1), Y1.1
/MCU/OSC2: C5.2, U3.10 (RA6/OSC2), Y1.2
/MCU/VALVE_CONTROL: U3.26 (RB5); also elsewhere on the board
/MCU/VBAT: U3.2 (RA0); also elsewhere on the board
/MCU/~MCLR: J3.5, R4.2, U3.1 (~MCLR)
CANH: U2.7 (CANH); also elsewhere on the board
CANL: U2.6 (CANL); also elsewhere on the board
GND: C2.1, C3.2, C4.2, C5.1, J3.3, U2.2 (VSS), U2.8 (STBY), U3.8 (VSS), U3.19 (VSS); also elsewhere on the board
unnamed: D2.1 (K), R5.1
unnamed: D3.1 (K), R6.1
unnamed: D4.1 (K), R7.1
unnamed: R5.2, U3.15 (RC4)
unnamed: R6.2, U3.14 (RC3)
unnamed: R7.2, U3.13 (RC2)

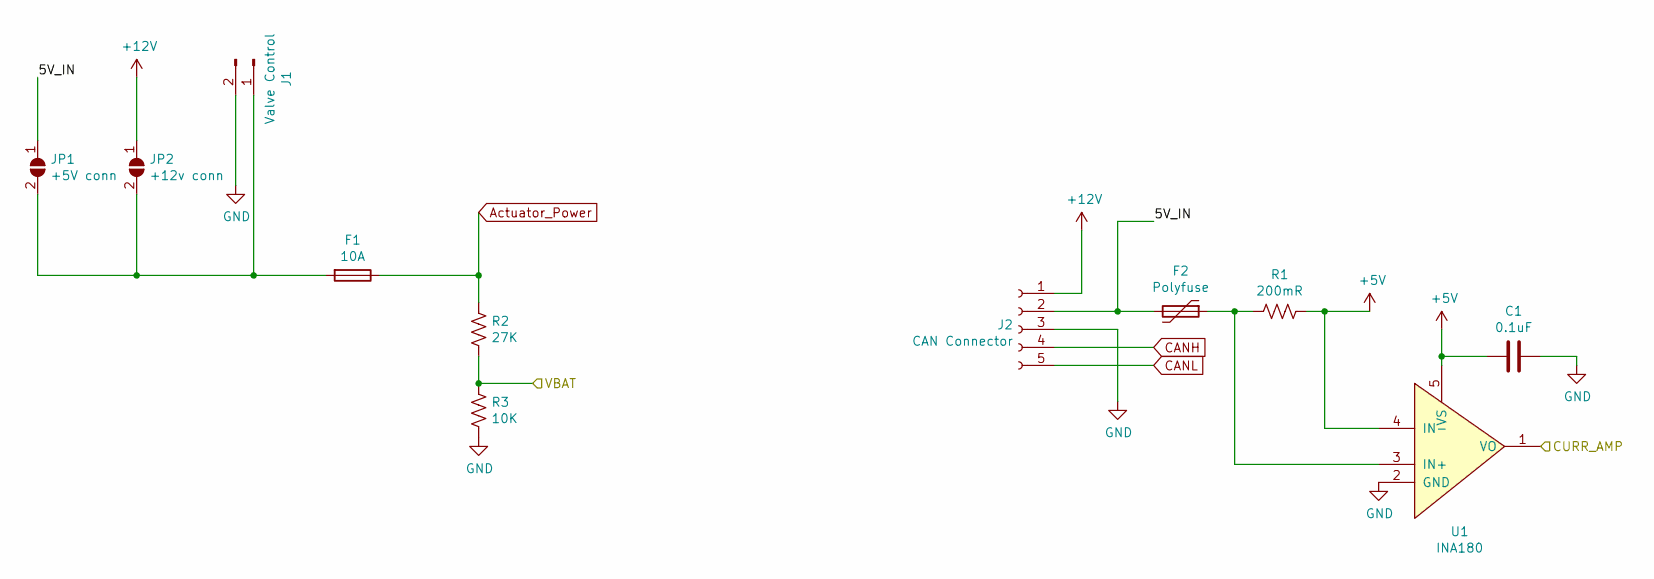
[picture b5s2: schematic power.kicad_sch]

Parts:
C1: 0.1uF; C_0805_2012Metric
F1: 10A; Fuseholder_36-3557-15-ND
F2: Polyfuse; Fuse_1206_3216Metric_Pad1.42x1.75mm_HandSolder
J1: Valve Control; JST_EH_B2B-EH-A_1x02_P2.50mm_Vertical
J2: CAN Connector; connector_Harwin_M80-5000642
JP1: +5V conn; SolderJumper-2_P1.3mm_Open_RoundedPad1.0x1.5mm
JP2: +12v conn; SolderJumper-2_P1.3mm_Open_RoundedPad1.0x1.5mm
R1: 200mR; R_1206_3216Metric
R2: 27K; R_0805_2012Metric
R3: 10K; R_0805_2012Metric
U1: INA180; SOT-23-5_HandSoldering

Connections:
+5V: C1.2, R1.1, U1.4 (IN-), U1.5 (VS); also elsewhere on the board
+12V: J2.1, JP2.1 (A)
/MCU/CURR_AMP: U1.1 (VO); also elsewhere on the board
/MCU/VBAT: R2.2, R3.1; also elsewhere on the board
/Power/5V_IN: F2.2, J2.2, JP1.1 (A)
Actuator_Power: F1.1, R2.1; also elsewhere on the board
CANH: J2.4; also elsewhere on the board
CANL: J2.5; also elsewhere on the board
GND: C1.1, J1.2, J2.3, R3.2, U1.2 (GND); also elsewhere on the board
unnamed: F1.2, J1.1, JP1.2 (B), JP2.2 (B)
unnamed: F2.1, R1.2, U1.3 (IN+)
